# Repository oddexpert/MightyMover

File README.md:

# MightyMover
Senior Design Project of an autonomous auto-following wagon.
## The Problem
Everyone has trouble carrying objects.  ​

​
What solutions are there for the physically challenged?​

Even wagons need to be pushed and pulled which causes strain on the body.​
## The Solution​
A product that will get the user's items to and from without interacting with the cart.​

​
​The MightyMover system is a two-component system. It includes the user’s phone and the mover. ​

The user’s phone will have an app compatible with the MightyMover. The user will send instructions and get feedback over a Bluetooth connection. ​

The Raspberry Pi will process the Bluetooth communication, object detection code, and PWM output (for the motors). ​

The MightyMover includes subsystems such as: ​

Phone-to-MightyMover Communications ​

MightyMover Motor Control System ​

Image recognition for obstacle avoidance

Software Hub Design and Battery Management.  ​

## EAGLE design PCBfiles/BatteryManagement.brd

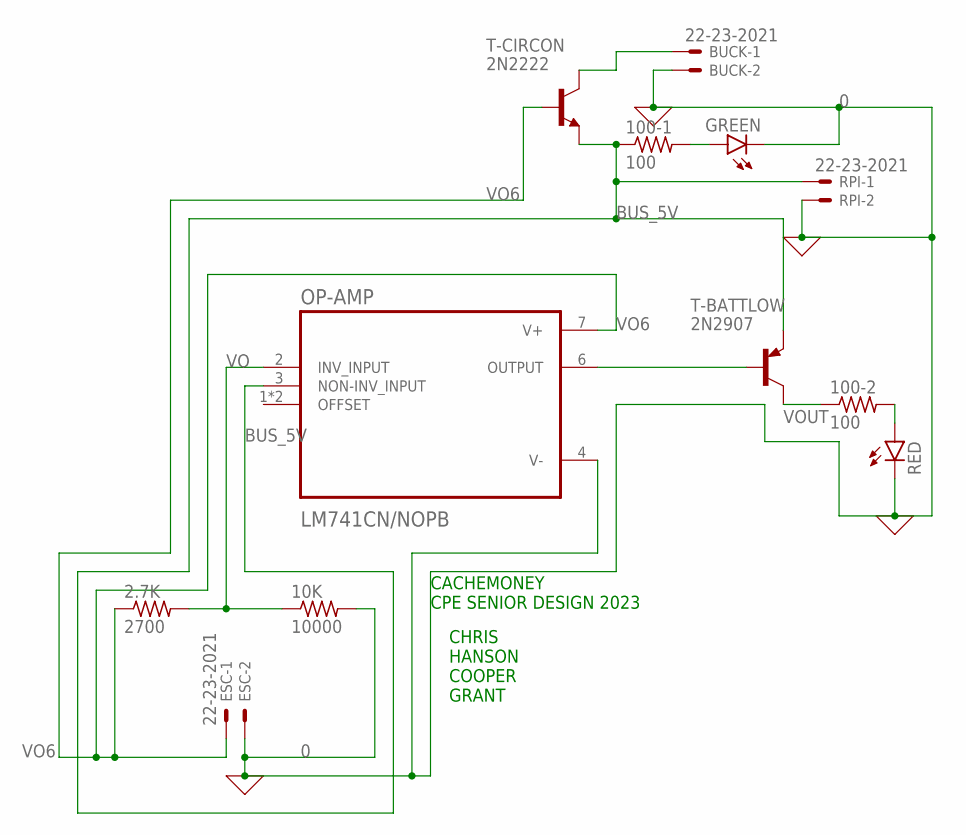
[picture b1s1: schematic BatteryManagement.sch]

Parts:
2.7K: 2700; 0204/7
10K: 10000; 0204/7
100-1, 100-2: 100; 0204/7
BUCK: 22-23-2021
ESC: 22-23-2021
GREEN: LED5MM
OP-AMP: LM741CN/NOPB; DIP794W45P254L959H508Q8
RED: LED5MM
RPI: 22-23-2021
T-BATTLOW: 2N2907; TO18
T-CIRCON: 2N2222; TO18

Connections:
0: 10K.2, BUCK.2, ESC.2, GREEN.K (C), OP-AMP.4 (V-), RED.K (C), RPI.2
BUS_5V: 100-1.1, OP-AMP.3 (NON-INV_INPUT), RPI.1, T-BATTLOW.1 (E), T-CIRCON.1 (E)
unnamed: BUCK.1, T-CIRCON.3 (C)
unnamed: 100-1.2, GREEN.A
unnamed: OP-AMP.6 (OUTPUT), T-BATTLOW.2 (B)
unnamed: 100-2.2, RED.A
VO: 2.7K.2, 10K.1, OP-AMP.2 (INV_INPUT)
VO6: 2.7K.1, ESC.1, OP-AMP.7 (V+), T-CIRCON.2 (B)
VOUT: 100-2.1, T-BATTLOW.3 (C)

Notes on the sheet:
CACHEMONEY CPE SENIOR DESIGN 2023
CHRIS HANSON COOPER GRANT

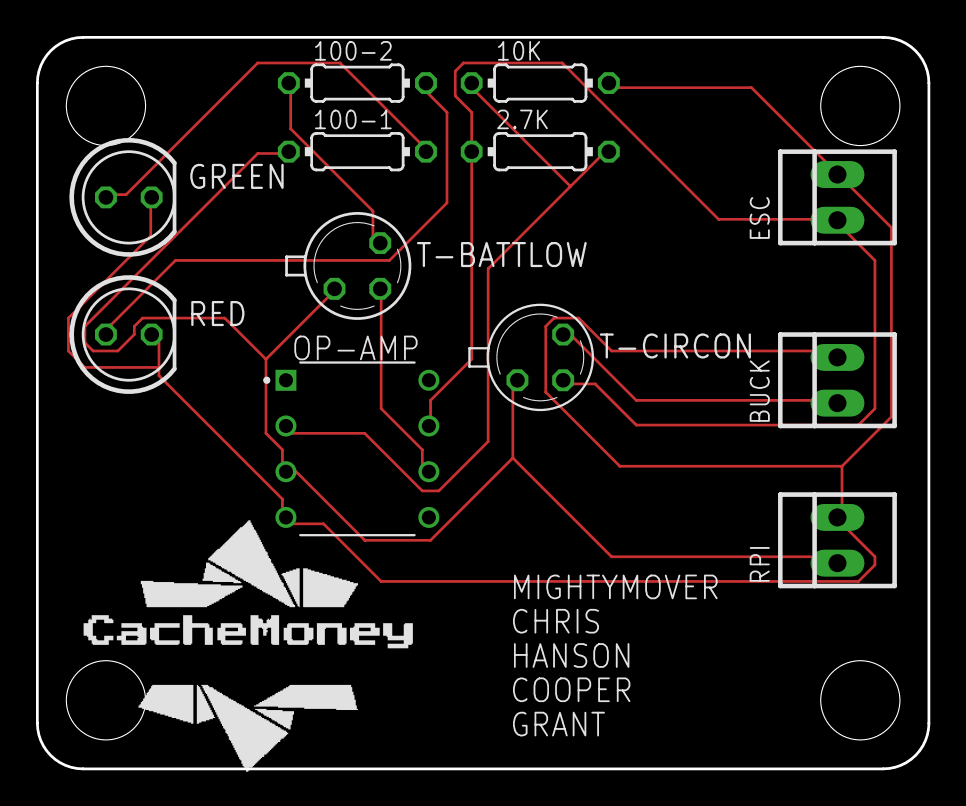
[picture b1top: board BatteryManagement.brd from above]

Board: 2 copper layers, 49.5 x 40.6 mm, 12 parts (0 on the bottom side), 9 nets.

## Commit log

2023-06-01 Create test
2023-06-01 Create name_placement
    initialize phone app folder
2023-06-01 Create place_holder
2023-06-01 Create name_holder
2023-10-26 Added Eagle Board and Schematic
2023-10-26 Messing with README syntax stuff
2023-10-30 Added folders and object detection code
2023-10-30 poopy.txt
2023-10-30 Revert "poopy.txt"
    This reverts commit 3912e6323e0b65a39d8f07dbae7094d976c69160.
2023-11-01 BT Comm Code
2023-11-01 Angle Updates
2023-11-01 im posting
2023-11-01 Create MIGHTYMOVER.ino
    this is for doing arduino stuff :)
2023-11-06 Delete Arduino-Codes directory
    We do not need this anymore
2023-12-03 New Object Detection
    wooo
2023-12-04 new Arduino
    wooo twice
